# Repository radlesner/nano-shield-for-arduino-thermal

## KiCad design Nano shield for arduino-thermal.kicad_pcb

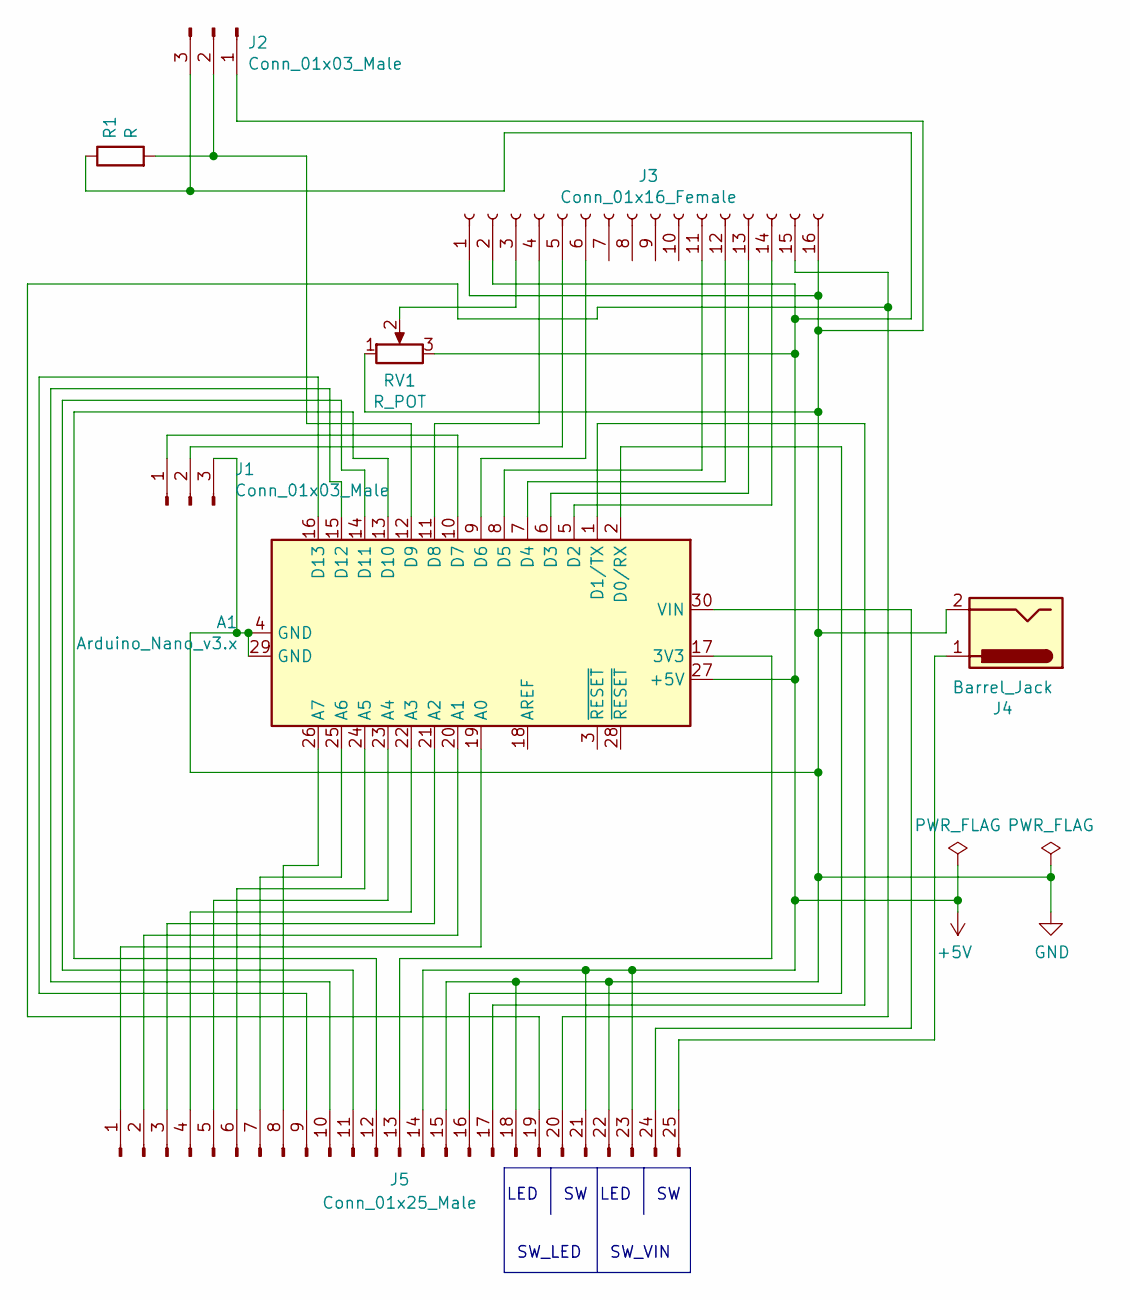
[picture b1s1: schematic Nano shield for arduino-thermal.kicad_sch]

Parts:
A1: Arduino_Nano_v3.x; Arduino_Nano
J1, J2: Conn_01x03_Male; PinHeader_1x03_P2.54mm_Vertical
J3: Conn_01x16_Female; PinSocket_1x16_P2.54mm_Vertical
J4: Barrel_Jack; BarrelJack_Horizontal
J5: Conn_01x25_Male; PinHeader_1x25_P2.54mm_Vertical
R1: R; R_Axial_DIN0204_L3.6mm_D1.6mm_P7.62mm_Horizontal
RV1: R_POT; Potentiometer_Piher_PT-6-V_Vertical

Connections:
+5V: A1.27 (+5V), J2.3, J3.2, J5.14, J5.21, J5.23, R1.1, RV1.3
GND: A1.4 (GND), A1.29 (GND), J1.3, J2.1, J3.1, J3.16, J4.2, J5.15, J5.18, J5.22, RV1.1
unnamed: A1.1 (D1/TX), J5.17
unnamed: A1.2 (D0/RX), J5.16
unnamed: A1.5 (D2), J3.14
unnamed: A1.6 (D3), J3.13
unnamed: A1.7 (D4), J3.12
unnamed: A1.8 (D5), J3.11
unnamed: A1.9 (D6), J3.6
unnamed: A1.10 (D7), J1.1
unnamed: A1.11 (D8), J3.4
unnamed: A1.12 (D9), J2.2, R1.2
unnamed: A1.13 (D10), J5.12
unnamed: A1.14 (D11), J5.11
unnamed: A1.15 (D12), J5.10
unnamed: A1.16 (D13), J5.9
unnamed: A1.17 (3V3), J5.13
unnamed: A1.19 (A0), J5.1
unnamed: A1.20 (A1), J5.2
unnamed: A1.21 (A2), J5.3
unnamed: A1.22 (A3), J5.4
unnamed: A1.23 (A4), J5.5
unnamed: A1.24 (A5), J5.6
unnamed: A1.25 (A6), J5.7
unnamed: A1.26 (A7), J5.8
unnamed: A1.30 (VIN), J5.24
unnamed: J1.2, J3.5
unnamed: J3.3, RV1.2
unnamed: J3.15, J5.19, J5.20
unnamed: J4.1, J5.25

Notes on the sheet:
SW_LED
LED
SW_VIN

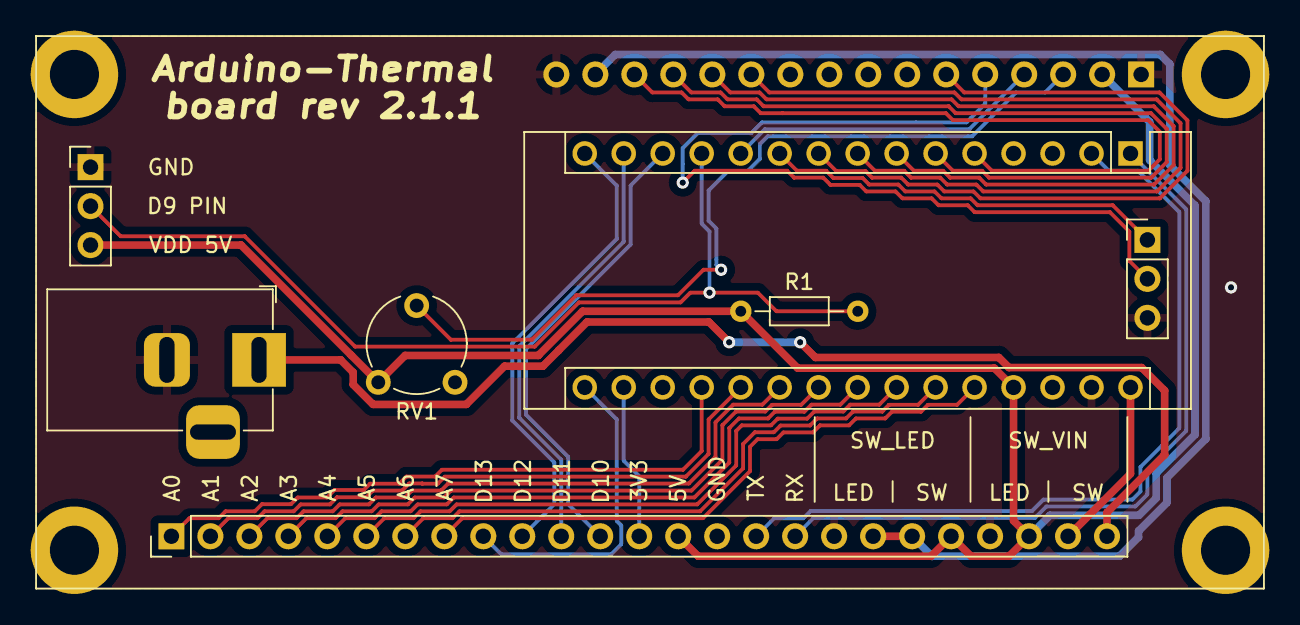
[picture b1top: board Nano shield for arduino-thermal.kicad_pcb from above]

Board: 2 copper layers, 8 parts (1 on the bottom side), 30 nets.

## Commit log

2023-04-04 Revision 2.0
2023-04-16 Revision 2.1.1 - Some paths have been changed
